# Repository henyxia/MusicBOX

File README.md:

MusicBOX
========

MusicBOX is a project I work on to provide audio amplification for my workshop.
It is split in independent parts. I try to improve all parts to improve quality
and features over time.

It relies on open source work (as much software as hardware). The main UI is
controlled a Raspberry PI and other functions are handled by an Arduino Uno.

Current status
--------------

The project is currently in work in progress and should be updated as soon as I
can improve a part. Here is a summary of each part status.

Part | Prototype | Design | Finished | Comment
-----|-----------|--------|----------|--------
Power Supply | :heavy_multiplication_x: | :heavy_multiplication_x: | :heavy_multiplication_x: | Currently using my lab power supply
Audio Amplifier | :white_check_mark: | :white_check_mark: |  :white_check_mark: | Using STA540 Kit for now
Source Selector | :white_check_mark: | :white_check_mark: | :heavy_multiplication_x: | Sent to manufacturer
Motor Controller | :heavy_multiplication_x: | :heavy_multiplication_x: | :heavy_multiplication_x: |
User Interface | :soon: |  :heavy_multiplication_x: | :heavy_multiplication_x: |

Source Selector
---------------

The source selector is an extension of the Arduino Uno. It is controlled with
digital pins 11, 12 and 13. It uses a decoder to select one (or none) of the 4
available inputs.

Document | File
---------|-----
Schematic | [File](musicbox.sch)
PCB | [File](musicbox.kicad_pcb)
BOM | [File](bom.csv)

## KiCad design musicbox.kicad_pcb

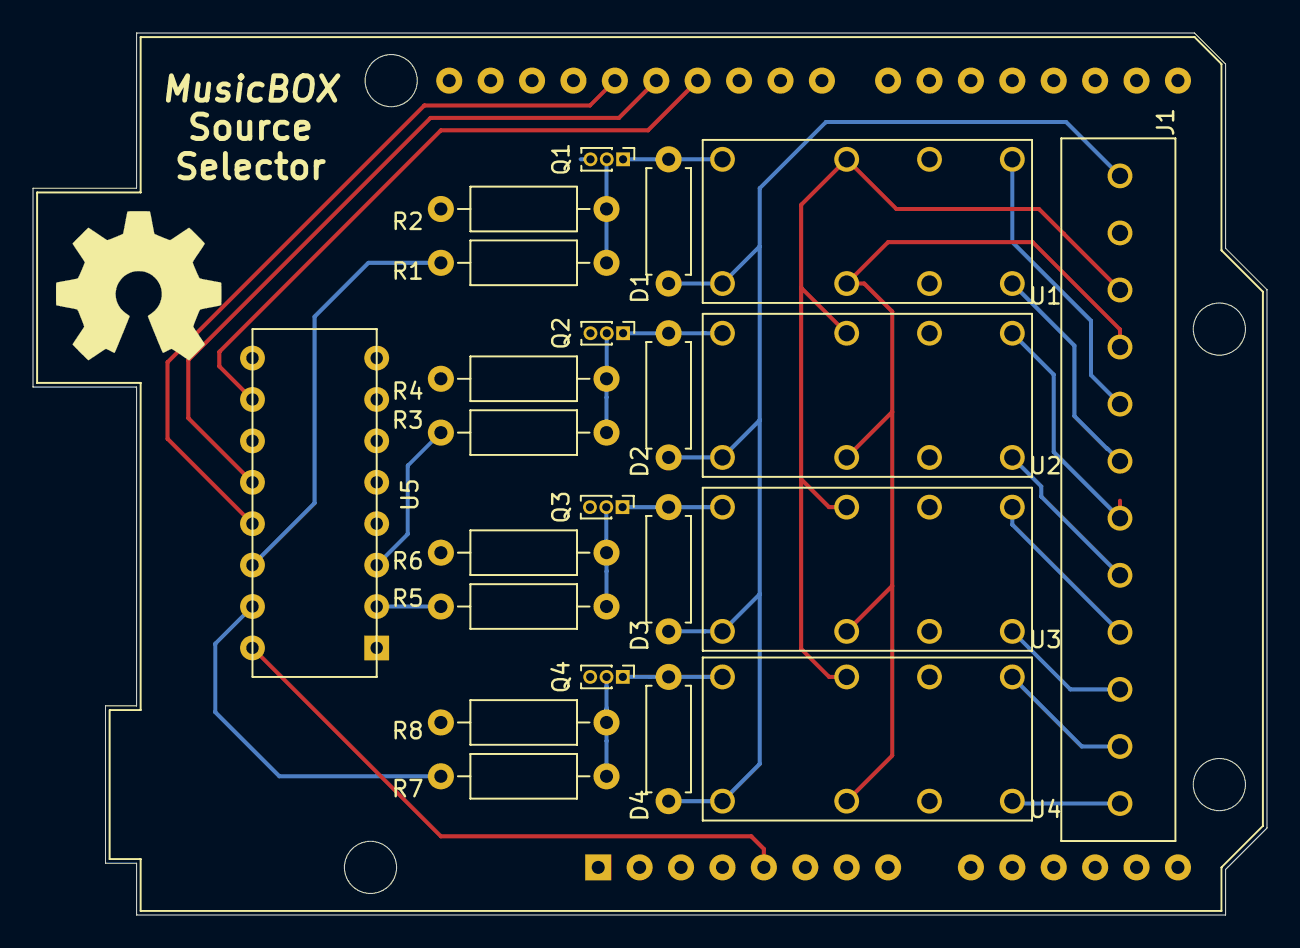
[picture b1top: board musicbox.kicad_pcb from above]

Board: 2 copper layers, 75.7 x 54.1 mm, 23 parts (0 on the bottom side), 28 nets.

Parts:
A1: Arduino_UNO_R3; Arduino_UNO_R3_WithMountingHoles
D1, D2, D3, D4: D; R_Axial_DIN0207_L6.3mm_D2.5mm_P7.62mm_Horizontal
J1: Screw_Terminal_01x12; OSTTE120104
Q1, Q2, Q3, Q4: Q_NPN_CBE; PinHeader_1x03_P1.00mm_Vertical
R1, R2, R3, R4, R5, R6, R7, R8: 10k; R_Axial_DIN0207_L6.3mm_D2.5mm_P10.16mm_Horizontal
U1, U2, U3, U4: V23105A5301A201*; Axicom_D2n_Relay_V23105
U5: CD4028BE

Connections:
/Source Selector/5V: D1.1, D2.1, D3.1, D4.1, J1.1, U1.1, U2.1, U3.1, U4.1
/Source Selector/LIN1: J1.5, U1.9
/Source Selector/LIN2: J1.7, U2.9
/Source Selector/LIN3: J1.9, U3.9
/Source Selector/LIN4: J1.11, U4.9
/Source Selector/LOUT: J1.3, U1.13, U2.13, U3.13, U4.13
/Source Selector/RIN1: J1.6, U1.8
/Source Selector/RIN2: J1.8, U2.8
/Source Selector/RIN3: J1.10, U3.8
/Source Selector/RIN4: J1.12, U4.8
/Source Selector/ROUT: J1.4, U1.4, U2.4, U3.4, U4.4
/Source Selector/SELSRC1: R1.2, U5.14
/Source Selector/SELSRC2: R3.2, U5.3
/Source Selector/SELSRC3: R5.2, U5.2
/Source Selector/SELSRC4: R7.2, U5.15
/Source Selector/SELSRCGND: A1.6, A1.7, A1.29, J1.2, Q1.3, Q2.3, Q3.3, Q4.3, R2.1, R4.1, R6.1, R8.1, U5.8, U5.11
unnamed: A1.5, U5.16
unnamed: A1.26, U5.10
unnamed: A1.27, U5.12
unnamed: A1.28, U5.13
unnamed: D1.2, Q1.1, U1.16
unnamed: D2.2, Q2.1, U2.16
unnamed: D3.2, Q3.1, U3.16
unnamed: D4.2, Q4.1, U4.16
unnamed: Q1.2, R1.1, R2.2
unnamed: Q2.2, R3.1, R4.2
unnamed: Q3.2, R5.1, R6.2
unnamed: Q4.2, R7.1, R8.2

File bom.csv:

"Id";"Designator";"Package";"Quantity";"Designation";"Supplier and ref";
1;"G***";"OSHW_SILK_FRONT_10MM";1;"LOGO";;;
2;"A1";"Arduino_UNO_R3_WithMountingHoles";1;"Arduino_UNO_R3";;;
3;"R8,R1,R2,R3,R4,R5,R6,R7";"R_Axial_DIN0207_L6.3mm_D2.5mm_P10.16mm_Horizontal";8;"10k";;;
4;"J1";"OSTTE120104";1;"Screw_Terminal_01x12";;;
5;"U2,U4,U3,U1";"Axicom_D2n_Relay_V23105";4;"V23105A5301A201*";;;
6;"D1,D2,D3,D4";"R_Axial_DIN0207_L6.3mm_D2.5mm_P7.62mm_Horizontal";4;"D";;;
7;"U5";"CD4028BE";1;"CD4028BE";;;
8;"Q4,Q3,Q2,Q1";"PinHeader_1x03_P1.00mm_Vertical";4;"Q_NPN_CBE";;;

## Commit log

2020-02-23 feat(source-selector): add first version
